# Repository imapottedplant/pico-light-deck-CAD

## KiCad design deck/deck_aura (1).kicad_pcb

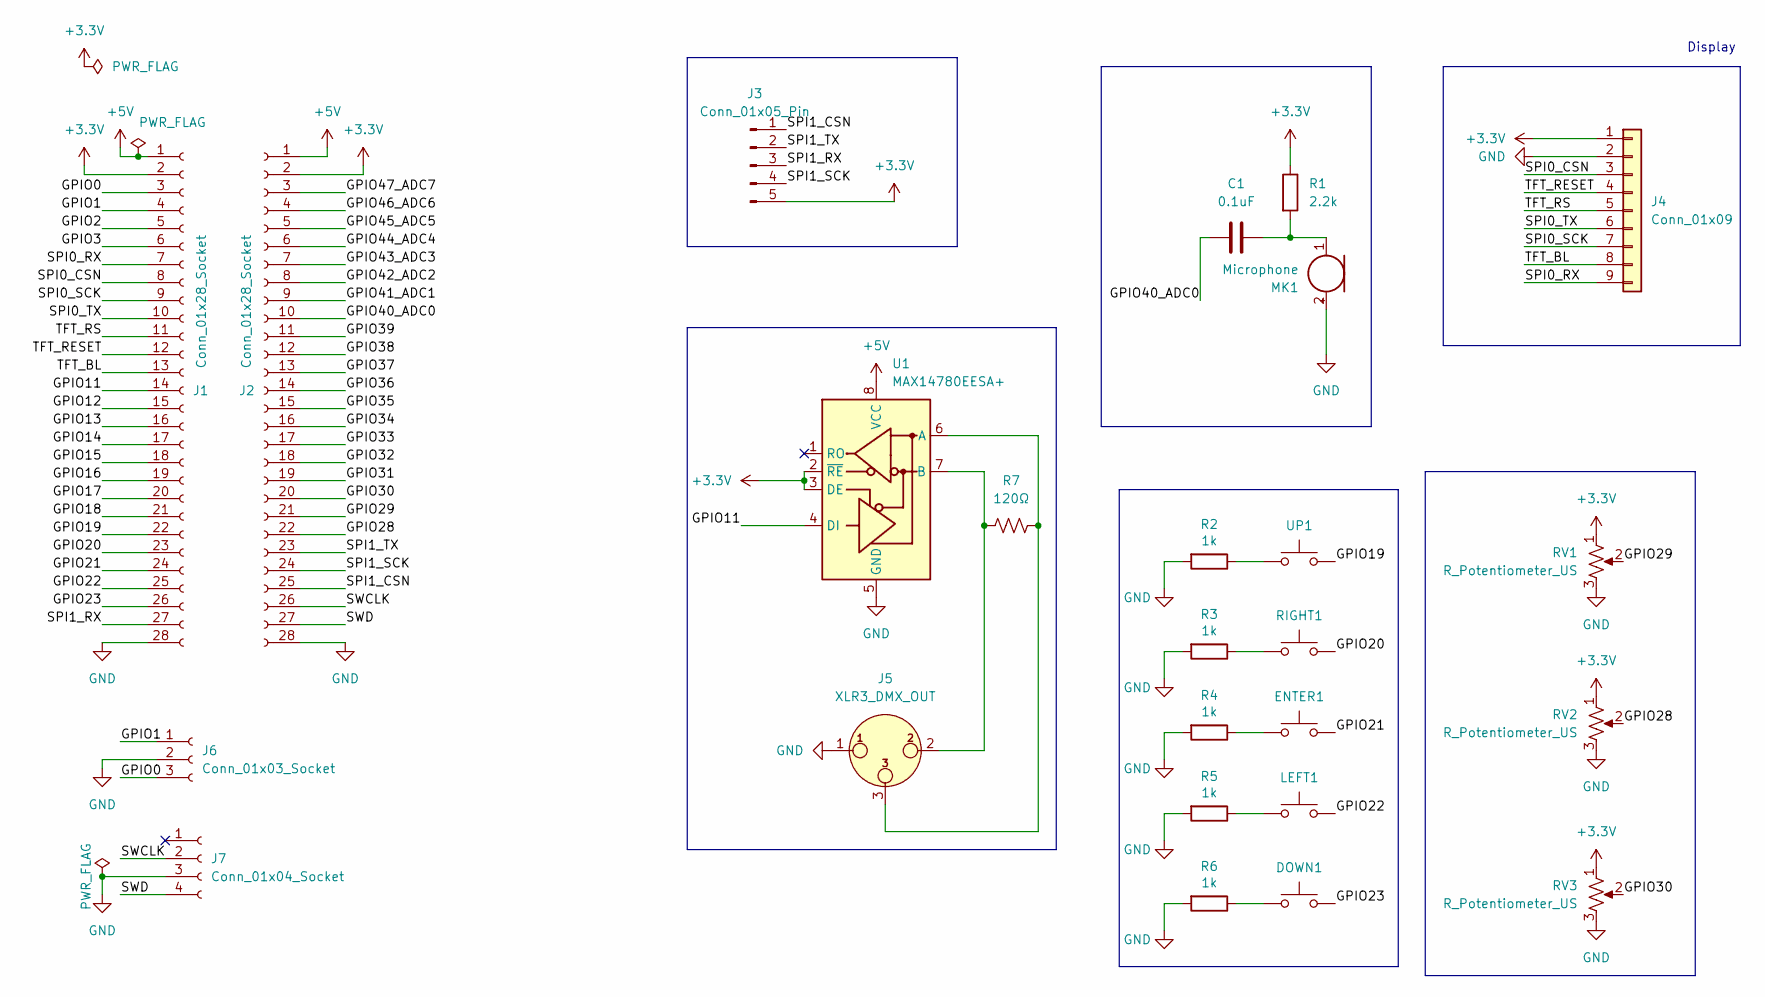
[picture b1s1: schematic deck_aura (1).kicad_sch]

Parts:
C1: 0.1uF; C_0805_2012Metric
DOWN1: SW_SPST_PTS647_Sx38; MPN PTS647SM38SMTR2 LFS
ENTER1: SW_SPST_PTS647_Sx38; MPN PTS647SM38SMTR2 LFS
J1, J2: Conn_01x28_Socket; PinSocket_1x28_P2.54mm_Vertical
J3: Conn_01x05_Pin; PinSocket_1x05_P2.54mm_Vertical
J4: Conn_01x09; PinSocket_1x09_P2.54mm_Vertical
J5: XLR3_DMX_OUT; Jack_XLR_Neutrik_NC3FAAH2-0_Horizontal
J6: Conn_01x03_Socket; PinSocket_1x03_P2.54mm_Vertical
J7: Conn_01x04_Socket; PinSocket_1x04_P2.54mm_Vertical
LEFT1: SW_SPST_PTS647_Sx38; MPN PTS647SM38SMTR2 LFS
MK1: Microphone; TerminalBlock_Phoenix_MKDS-1,5-2-5.08_1x02_P5.08mm_Horizont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
R1: 2.2k; R_0805_2012Metric
R2, R3, R4, R5, R6: 1k; R_0805_2012Metric; MPN RC0402JR-071KL
R7: 120Ω; R_0805_2012Metric
RIGHT1: SW_SPST_PTS647_Sx38; MPN PTS647SM38SMTR2 LFS
RV1, RV2, RV3: R_Potentiometer_US; Potentiometer_Vishay_T73YP_Vertical
U1: MAX14780EESA+; SOIC-8_3.9x4.9mm_P1.27mm
UP1: SW_SPST_PTS647_Sx38; MPN PTS647SM38SMTR2 LFS

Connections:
+3.3V: J1.2, J2.2, J3.5, J4.1, R1.1, RV1.1, RV2.1, RV3.1, U1.2 (~RE), U1.3 (DE)
+5V: J1.1, J2.1, U1.8 (VCC)
/GPIO0: J1.3, J6.3
/GPIO1: J1.4, J6.1
/GPIO2: J1.5
/GPIO3: J1.6
/GPIO11: J1.14, U1.4 (DI)
/GPIO12: J1.15
/GPIO13: J1.16
/GPIO14: J1.17
/GPIO15: J1.18
/GPIO16: J1.19
/GPIO17: J1.20
/GPIO18: J1.21
/GPIO19: J1.22, UP1.2
/GPIO20: J1.23, RIGHT1.2
/GPIO21: ENTER1.2, J1.24
/GPIO22: J1.25, LEFT1.2
/GPIO23: DOWN1.2, J1.26
/GPIO28: J2.22, RV2.2
/GPIO29: J2.21, RV1.2
/GPIO30: J2.20, RV3.2
/GPIO31: J2.19
/GPIO32: J2.18
/GPIO33: J2.17
/GPIO34: J2.16
/GPIO35: J2.15
/GPIO36: J2.14
/GPIO37: J2.13
/GPIO38: J2.12
/GPIO39: J2.11
/GPIO40_ADC0: C1.1, J2.10
/GPIO41_ADC1: J2.9
/GPIO42_ADC2: J2.8
/GPIO43_ADC3: J2.7
/GPIO44_ADC4: J2.6
/GPIO45_ADC5: J2.5
/GPIO46_ADC6: J2.4
/GPIO47_ADC7: J2.3
/SPI0_CSN: J1.8, J4.3
/SPI0_RX: J1.7, J4.9
/SPI0_SCK: J1.9, J4.7
/SPI0_TX: J1.10, J4.6
/SPI1_CSN: J2.25, J3.1
/SPI1_RX: J1.27, J3.3
/SPI1_SCK: J2.24, J3.4
/SPI1_TX: J2.23, J3.2
/SWCLK: J2.26, J7.2
/SWD: J2.27, J7.4
/TFT_BL: J1.13, J4.8
/TFT_RESET: J1.12, J4.4
/TFT_RS: J1.11, J4.5
GND: J1.28, J2.28, J4.2, J5.1, J6.2, J7.3, MK1.2 (+), R2.2, R3.2, R4.2, R5.2, R6.2, RV1.3, RV2.3, RV3.3, U1.5 (GND)
unnamed: DOWN1.1, R6.1
unnamed: ENTER1.1, R4.1
unnamed: LEFT1.1, R5.1
unnamed: C1.2, MK1.1 (-), R1.2
unnamed: R2.1, UP1.1
unnamed: R3.1, RIGHT1.1
unnamed: J5.3, R7.2, U1.6 (A)
unnamed: J5.2, R7.1, U1.7 (B)

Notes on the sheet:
Display

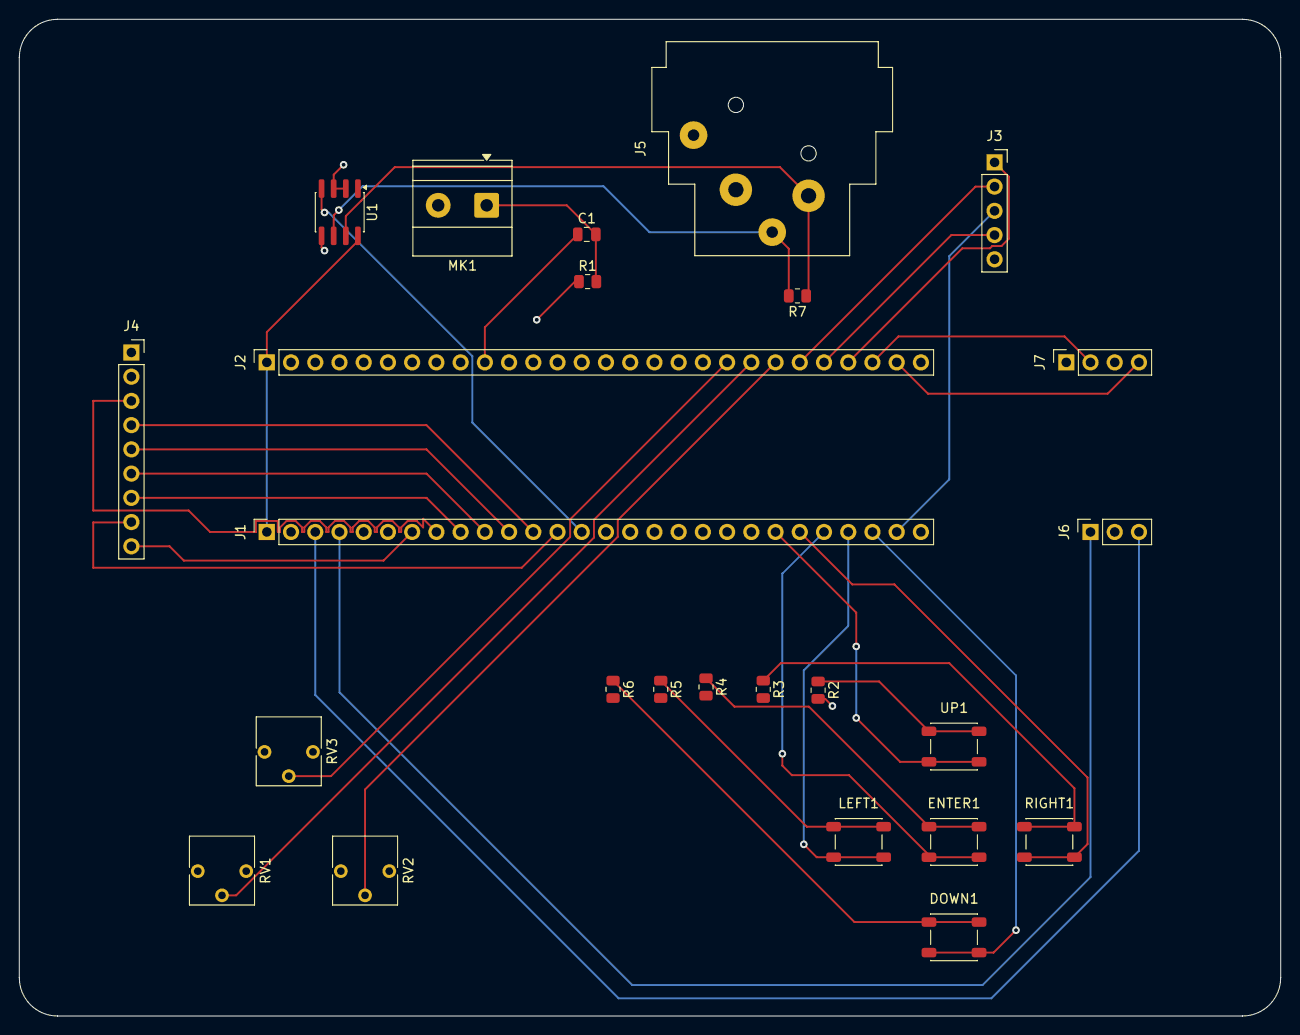
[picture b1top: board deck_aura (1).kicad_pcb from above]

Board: 4 copper layers, 132.2 x 104.5 mm, 25 parts (0 on the bottom side), 36 nets.
